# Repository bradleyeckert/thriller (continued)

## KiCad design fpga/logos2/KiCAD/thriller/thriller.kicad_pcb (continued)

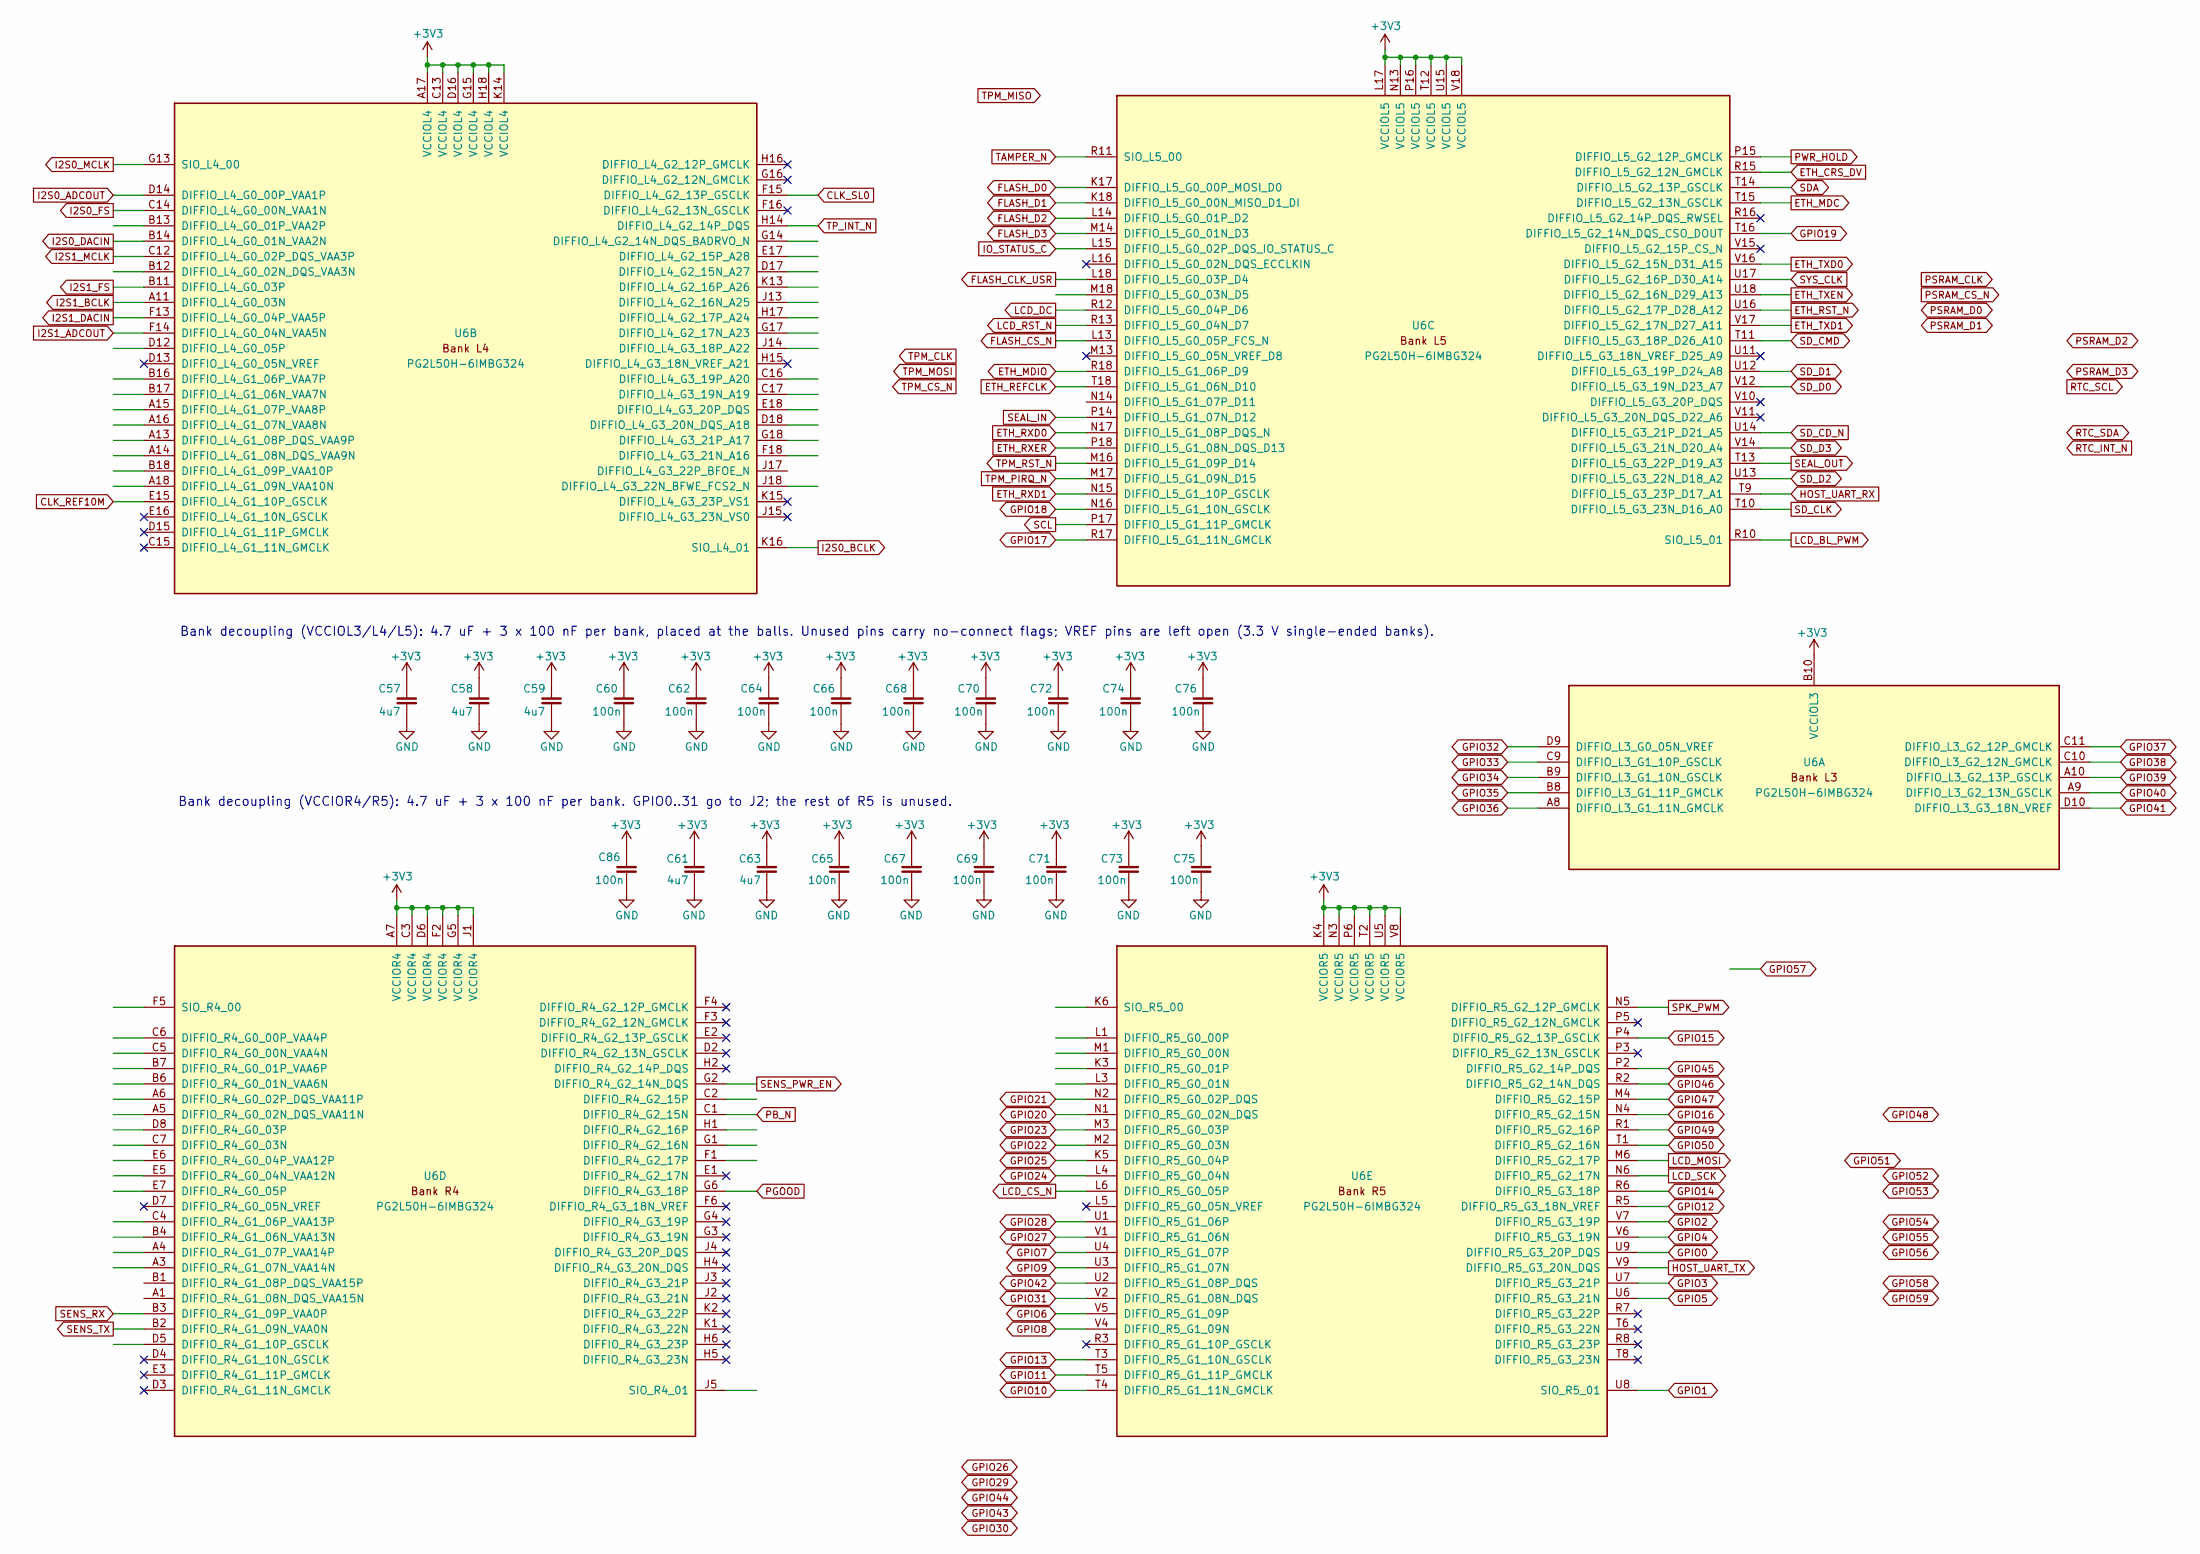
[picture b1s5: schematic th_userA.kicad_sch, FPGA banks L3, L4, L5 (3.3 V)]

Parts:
C57, C58, C59, C61, C63: 4u7; C_0603_1608Metric; LCSC C19666
C60, C62, C64, C65, C66, C67, C68, C69, C70, C71, C72, C73, C74, C75, C76, C86: 100n; C_0402_1005Metric; LCSC C1525
U6: PG2L50H-6IMBG324; BGA-324_15x15mm_Layout18x18_P0.8mm; MPN PG2L50H-6IMBG324

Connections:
CLK_REF10M: U6.E15 (DIFFIO_L4_G1_10P_GSCLK); also elsewhere on the board
CLK_SL0: U6.F15 (DIFFIO_L4_G2_13P_GSCLK); also elsewhere on the board
ETH_CRS_DV: U6.R15 (DIFFIO_L5_G2_12N_GMCLK); also elsewhere on the board
ETH_MDC: U6.T15 (DIFFIO_L5_G2_13N_GSCLK); also elsewhere on the board
ETH_MDIO: U6.R18 (DIFFIO_L5_G1_06P_D9); also elsewhere on the board
ETH_REFCLK: U6.T18 (DIFFIO_L5_G1_06N_D10); also elsewhere on the board
ETH_RST_N: U6.U16 (DIFFIO_L5_G2_17P_D28_A12); also elsewhere on the board
ETH_RXD0: U6.N17 (DIFFIO_L5_G1_08P_DQS_N); also elsewhere on the board
ETH_RXD1: U6.N15 (DIFFIO_L5_G1_10P_GSCLK); also elsewhere on the board
ETH_RXER: U6.P18 (DIFFIO_L5_G1_08N_DQS_D13); also elsewhere on the board
ETH_TXD0: U6.V16 (DIFFIO_L5_G2_15N_D31_A15); also elsewhere on the board
ETH_TXD1: U6.V17 (DIFFIO_L5_G2_17N_D27_A11); also elsewhere on the board
ETH_TXEN: U6.U18 (DIFFIO_L5_G2_16N_D29_A13); also elsewhere on the board
FLASH_CLK_USR: U6.L18 (DIFFIO_L5_G0_03P_D4); also elsewhere on the board
FLASH_CS_N: U6.L13 (DIFFIO_L5_G0_05P_FCS_N); also elsewhere on the board
FLASH_D0: U6.K17 (DIFFIO_L5_G0_00P_MOSI_D0); also elsewhere on the board
FLASH_D1: U6.K18 (DIFFIO_L5_G0_00N_MISO_D1_DI); also elsewhere on the board
FLASH_D2: U6.L14 (DIFFIO_L5_G0_01P_D2); also elsewhere on the board
FLASH_D3: U6.M14 (DIFFIO_L5_G0_01N_D3); also elsewhere on the board
GND: C57.2, C58.2, C59.2, C60.2, C61.2, C62.2, C63.2, C64.2, C65.2, C66.2, C67.2, C68.2, C69.2, C70.2, C71.2, C72.2, C73.2, C74.2, C75.2, C76.2, C86.2; also elsewhere on the board
GPIO0: U6.U9 (DIFFIO_R5_G3_20P_DQS); also elsewhere on the board
GPIO1: U6.U8 (SIO_R5_01); also elsewhere on the board
GPIO2: U6.V7 (DIFFIO_R5_G3_19P); also elsewhere on the board
GPIO3: U6.U7 (DIFFIO_R5_G3_21P); also elsewhere on the board
GPIO4: U6.V6 (DIFFIO_R5_G3_19N); also elsewhere on the board
GPIO5: U6.U6 (DIFFIO_R5_G3_21N); also elsewhere on the board
GPIO6: U6.V5 (DIFFIO_R5_G1_09P); also elsewhere on the board
GPIO7: U6.U4 (DIFFIO_R5_G1_07P); also elsewhere on the board
GPIO8: U6.V4 (DIFFIO_R5_G1_09N); also elsewhere on the board
GPIO9: U6.U3 (DIFFIO_R5_G1_07N); also elsewhere on the board
GPIO10: U6.T4 (DIFFIO_R5_G1_11N_GMCLK); also elsewhere on the board
GPIO11: U6.T5 (DIFFIO_R5_G1_11P_GMCLK); also elsewhere on the board
GPIO12: U6.R5 (DIFFIO_R5_G3_18N_VREF); also elsewhere on the board
GPIO13: U6.T3 (DIFFIO_R5_G1_10N_GSCLK); also elsewhere on the board
GPIO14: U6.R6 (DIFFIO_R5_G3_18P); also elsewhere on the board
GPIO15: U6.P4 (DIFFIO_R5_G2_13P_GSCLK); also elsewhere on the board
GPIO16: U6.N4 (DIFFIO_R5_G2_15N); also elsewhere on the board
GPIO17: U6.R17 (DIFFIO_L5_G1_11N_GMCLK); also elsewhere on the board
GPIO18: U6.N16 (DIFFIO_L5_G1_10N_GSCLK); also elsewhere on the board
GPIO19: U6.T16 (DIFFIO_L5_G2_14N_DQS_CSO_DOUT); also elsewhere on the board
GPIO20: U6.N1 (DIFFIO_R5_G0_02N_DQS); also elsewhere on the board
GPIO21: U6.N2 (DIFFIO_R5_G0_02P_DQS); also elsewhere on the board
GPIO22: U6.M2 (DIFFIO_R5_G0_03N); also elsewhere on the board
GPIO23: U6.M3 (DIFFIO_R5_G0_03P); also elsewhere on the board
GPIO24: U6.L4 (DIFFIO_R5_G0_04N); also elsewhere on the board
GPIO25: U6.K5 (DIFFIO_R5_G0_04P); also elsewhere on the board
GPIO27: U6.V1 (DIFFIO_R5_G1_06N); also elsewhere on the board
GPIO28: U6.U1 (DIFFIO_R5_G1_06P); also elsewhere on the board
GPIO31: U6.V2 (DIFFIO_R5_G1_08N_DQS); also elsewhere on the board
GPIO32: U6.D9 (DIFFIO_L3_G0_05N_VREF); also elsewhere on the board
GPIO33: U6.C9 (DIFFIO_L3_G1_10P_GSCLK); also elsewhere on the board
GPIO34: U6.B9 (DIFFIO_L3_G1_10N_GSCLK); also elsewhere on the board
GPIO35: U6.B8 (DIFFIO_L3_G1_11P_GMCLK); also elsewhere on the board
GPIO36: U6.A8 (DIFFIO_L3_G1_11N_GMCLK); also elsewhere on the board
GPIO37: U6.C11 (DIFFIO_L3_G2_12P_GMCLK); also elsewhere on the board
GPIO38: U6.C10 (DIFFIO_L3_G2_12N_GMCLK); also elsewhere on the board
GPIO39: U6.A10 (DIFFIO_L3_G2_13P_GSCLK); also elsewhere on the board
GPIO40: U6.A9 (DIFFIO_L3_G2_13N_GSCLK); also elsewhere on the board
GPIO41: U6.D10 (DIFFIO_L3_G3_18N_VREF); also elsewhere on the board
GPIO42: U6.U2 (DIFFIO_R5_G1_08P_DQS); also elsewhere on the board
GPIO45: U6.P2 (DIFFIO_R5_G2_14P_DQS); also elsewhere on the board
GPIO46: U6.R2 (DIFFIO_R5_G2_14N_DQS); also elsewhere on the board
GPIO47: U6.M4 (DIFFIO_R5_G2_15P); also elsewhere on the board
GPIO49: U6.R1 (DIFFIO_R5_G2_16P); also elsewhere on the board
GPIO50: U6.T1 (DIFFIO_R5_G2_16N); also elsewhere on the board
HOST_UART_RX: U6.T9 (DIFFIO_L5_G3_23P_D17_A1); also elsewhere on the board
HOST_UART_TX: U6.V9 (DIFFIO_R5_G3_20N_DQS); also elsewhere on the board
I2S0_ADCOUT: U6.D14 (DIFFIO_L4_G0_00P_VAA1P); also elsewhere on the board
I2S0_BCLK: U6.K16 (SIO_L4_01); also elsewhere on the board
I2S0_DACIN: U6.B14 (DIFFIO_L4_G0_01N_VAA2N); also elsewhere on the board
I2S0_FS: U6.C14 (DIFFIO_L4_G0_00N_VAA1N); also elsewhere on the board
I2S0_MCLK: U6.G13 (SIO_L4_00); also elsewhere on the board
I2S1_ADCOUT: U6.F14 (DIFFIO_L4_G0_04N_VAA5N); also elsewhere on the board
I2S1_BCLK: U6.A11 (DIFFIO_L4_G0_03N); also elsewhere on the board
I2S1_DACIN: U6.F13 (DIFFIO_L4_G0_04P_VAA5P); also elsewhere on the board
I2S1_FS: U6.B11 (DIFFIO_L4_G0_03P); also elsewhere on the board
I2S1_MCLK: U6.C12 (DIFFIO_L4_G0_02P_DQS_VAA3P); also elsewhere on the board
IO_STATUS_C: U6.L15 (DIFFIO_L5_G0_02P_DQS_IO_STATUS_C); also elsewhere on the board
LCD_BL_PWM: U6.R10 (SIO_L5_01); also elsewhere on the board
LCD_CS_N: U6.L6 (DIFFIO_R5_G0_05P); also elsewhere on the board
LCD_DC: U6.R12 (DIFFIO_L5_G0_04P_D6); also elsewhere on the board
LCD_MOSI: U6.M6 (DIFFIO_R5_G2_17P); also elsewhere on the board
LCD_RST_N: U6.R13 (DIFFIO_L5_G0_04N_D7); also elsewhere on the board
LCD_SCK: U6.N6 (DIFFIO_R5_G2_17N); also elsewhere on the board
PB_N: U6.C1 (DIFFIO_R4_G2_15N); also elsewhere on the board
PGOOD: U6.G6 (DIFFIO_R4_G3_18P); also elsewhere on the board
PWR_HOLD: U6.P15 (DIFFIO_L5_G2_12P_GMCLK); also elsewhere on the board
SCL: U6.P17 (DIFFIO_L5_G1_11P_GMCLK); also elsewhere on the board
SDA: U6.T14 (DIFFIO_L5_G2_13P_GSCLK); also elsewhere on the board
SD_CD_N: U6.U14 (DIFFIO_L5_G3_21P_D21_A5); also elsewhere on the board
SD_CLK: U6.T10 (DIFFIO_L5_G3_23N_D16_A0); also elsewhere on the board
SD_CMD: U6.T11 (DIFFIO_L5_G3_18P_D26_A10); also elsewhere on the board
SD_D0: U6.V12 (DIFFIO_L5_G3_19N_D23_A7); also elsewhere on the board
SD_D1: U6.U12 (DIFFIO_L5_G3_19P_D24_A8); also elsewhere on the board
SD_D2: U6.U13 (DIFFIO_L5_G3_22N_D18_A2); also elsewhere on the board
SD_D3: U6.V14 (DIFFIO_L5_G3_21N_D20_A4); also elsewhere on the board
SEAL_IN: U6.P14 (DIFFIO_L5_G1_07N_D12); also elsewhere on the board
SEAL_OUT: U6.T13 (DIFFIO_L5_G3_22P_D19_A3); also elsewhere on the board
SENS_PWR_EN: U6.G2 (DIFFIO_R4_G2_14N_DQS); also elsewhere on the board
SENS_RX: U6.B3 (DIFFIO_R4_G1_09P_VAA0P); also elsewhere on the board
SENS_TX: U6.B2 (DIFFIO_R4_G1_09N_VAA0N); also elsewhere on the board
SPK_PWM: U6.N5 (DIFFIO_R5_G2_12P_GMCLK); also elsewhere on the board
SYS_CLK: U6.U17 (DIFFIO_L5_G2_16P_D30_A14); also elsewhere on the board
TAMPER_N: U6.R11 (SIO_L5_00); also elsewhere on the board
TPM_PIRQ_N: U6.M17 (DIFFIO_L5_G1_09N_D15); also elsewhere on the board
TPM_RST_N: U6.M16 (DIFFIO_L5_G1_09P_D14); also elsewhere on the board
TP_INT_N: U6.H14 (DIFFIO_L4_G2_14P_DQS); also elsewhere on the board

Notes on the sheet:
Bank decoupling (VCCIOR4/R5): 4.7 uF + 3 x 100 nF per bank. GPIO0..31 go to J2; the rest of R5 is unused.
Bank decoupling (VCCIOL3/L4/L5): 4.7 uF + 3 x 100 nF per bank, placed at the balls. Unused pins carry no-connect flags; VREF pins are left open (3.3 V single-ended banks).

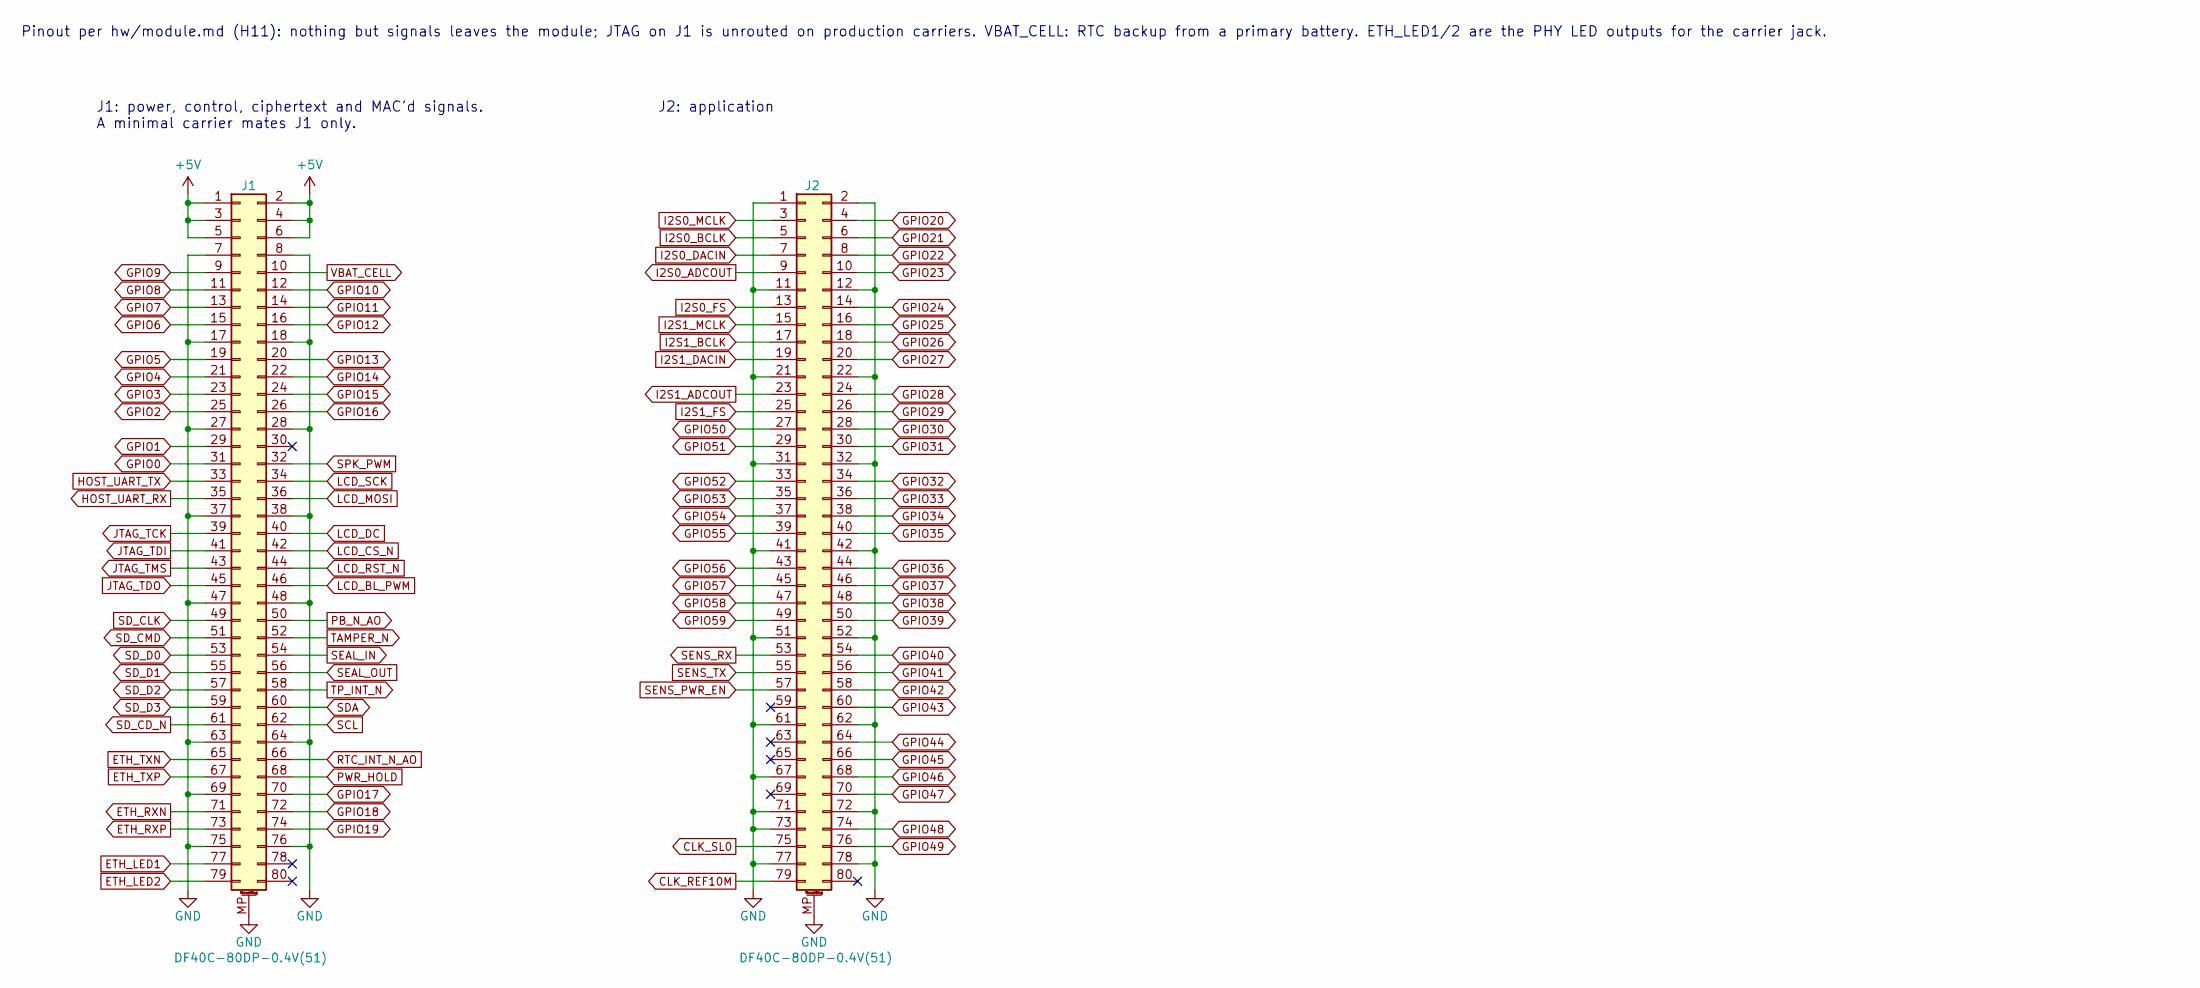
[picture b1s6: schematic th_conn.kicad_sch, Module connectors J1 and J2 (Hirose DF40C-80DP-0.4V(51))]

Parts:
J1, J2: DF40C-80DP-0.4V(51); Hirose_DF40C-80DP-0.4V_2x40-1MP_P0.4mm; MPN DF40C-80DP-0.4V(51)

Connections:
+5V: J1.1, J1.2, J1.3, J1.4, J1.5, J1.6; also elsewhere on the board
CLK_REF10M: J2.79; also elsewhere on the board
CLK_SL0: J2.75; also elsewhere on the board
ETH_LED1: J1.77; also elsewhere on the board
ETH_LED2: J1.79; also elsewhere on the board
ETH_RXN: J1.71; also elsewhere on the board
ETH_RXP: J1.73; also elsewhere on the board
ETH_TXN: J1.65; also elsewhere on the board
ETH_TXP: J1.67; also elsewhere on the board
GND: J1.7, J1.8, J1.17, J1.18, J1.27, J1.28, J1.37, J1.38, J1.47, J1.48, J1.63, J1.64, J1.69, J1.75, J1.76, J1.MP (MountPin), J2.1, J2.2, J2.11, J2.12, J2.21, J2.22, J2.31, J2.32, J2.41, J2.42, J2.51, J2.52, J2.61, J2.62, J2.67, J2.71, J2.72, J2.73, J2.77, J2.78, J2.MP (MountPin); also elsewhere on the board
GPIO0: J1.31; also elsewhere on the board
GPIO1: J1.29; also elsewhere on the board
GPIO2: J1.25; also elsewhere on the board
GPIO3: J1.23; also elsewhere on the board
GPIO4: J1.21; also elsewhere on the board
GPIO5: J1.19; also elsewhere on the board
GPIO6: J1.15; also elsewhere on the board
GPIO7: J1.13; also elsewhere on the board
GPIO8: J1.11; also elsewhere on the board
GPIO9: J1.9; also elsewhere on the board
GPIO10: J1.12; also elsewhere on the board
GPIO11: J1.14; also elsewhere on the board
GPIO12: J1.16; also elsewhere on the board
GPIO13: J1.20; also elsewhere on the board
GPIO14: J1.22; also elsewhere on the board
GPIO15: J1.24; also elsewhere on the board
GPIO16: J1.26; also elsewhere on the board
GPIO17: J1.70; also elsewhere on the board
GPIO18: J1.72; also elsewhere on the board
GPIO19: J1.74; also elsewhere on the board
GPIO20: J2.4; also elsewhere on the board
GPIO21: J2.6; also elsewhere on the board
GPIO22: J2.8; also elsewhere on the board
GPIO23: J2.10; also elsewhere on the board
GPIO24: J2.14; also elsewhere on the board
GPIO25: J2.16; also elsewhere on the board
GPIO26: J2.18
GPIO27: J2.20; also elsewhere on the board
GPIO28: J2.24; also elsewhere on the board
GPIO29: J2.26
GPIO30: J2.28
GPIO31: J2.30; also elsewhere on the board
GPIO32: J2.34; also elsewhere on the board
GPIO33: J2.36; also elsewhere on the board
GPIO34: J2.38; also elsewhere on the board
GPIO35: J2.40; also elsewhere on the board
GPIO36: J2.44; also elsewhere on the board
GPIO37: J2.46; also elsewhere on the board
GPIO38: J2.48; also elsewhere on the board
GPIO39: J2.50; also elsewhere on the board
GPIO40: J2.54; also elsewhere on the board
GPIO41: J2.56; also elsewhere on the board
GPIO42: J2.58; also elsewhere on the board
GPIO43: J2.60
GPIO44: J2.64
GPIO45: J2.66; also elsewhere on the board
GPIO46: J2.68; also elsewhere on the board
GPIO47: J2.70; also elsewhere on the board
GPIO48: J2.74
GPIO49: J2.76; also elsewhere on the board
GPIO50: J2.27; also elsewhere on the board
GPIO51: J2.29
GPIO52: J2.33
GPIO53: J2.35
GPIO54: J2.37
GPIO55: J2.39
GPIO56: J2.43
GPIO57: J2.45
GPIO58: J2.47
GPIO59: J2.49
HOST_UART_RX: J1.35; also elsewhere on the board
HOST_UART_TX: J1.33; also elsewhere on the board
I2S0_ADCOUT: J2.9; also elsewhere on the board
I2S0_BCLK: J2.5; also elsewhere on the board
I2S0_DACIN: J2.7; also elsewhere on the board
I2S0_FS: J2.13; also elsewhere on the board
I2S0_MCLK: J2.3; also elsewhere on the board
I2S1_ADCOUT: J2.23; also elsewhere on the board
I2S1_BCLK: J2.17; also elsewhere on the board
I2S1_DACIN: J2.19; also elsewhere on the board
I2S1_FS: J2.25; also elsewhere on the board
I2S1_MCLK: J2.15; also elsewhere on the board
JTAG_TCK: J1.39; also elsewhere on the board
JTAG_TDI: J1.41; also elsewhere on the board
JTAG_TDO: J1.45; also elsewhere on the board
JTAG_TMS: J1.43; also elsewhere on the board
LCD_BL_PWM: J1.46; also elsewhere on the board
LCD_CS_N: J1.42; also elsewhere on the board
LCD_DC: J1.40; also elsewhere on the board
LCD_MOSI: J1.36; also elsewhere on the board
LCD_RST_N: J1.44; also elsewhere on the board
LCD_SCK: J1.34; also elsewhere on the board
PB_N_AO: J1.50
PWR_HOLD: J1.68; also elsewhere on the board
RTC_INT_N_AO: J1.66
SCL: J1.62; also elsewhere on the board
SDA: J1.60; also elsewhere on the board
SD_CD_N: J1.61; also elsewhere on the board
SD_CLK: J1.49; also elsewhere on the board
SD_CMD: J1.51; also elsewhere on the board
SD_D0: J1.53; also elsewhere on the board
SD_D1: J1.55; also elsewhere on the board
SD_D2: J1.57; also elsewhere on the board
SD_D3: J1.59; also elsewhere on the board
SEAL_IN: J1.54; also elsewhere on the board
SEAL_OUT: J1.56; also elsewhere on the board
SENS_PWR_EN: J2.57; also elsewhere on the board
SENS_RX: J2.53; also elsewhere on the board
SENS_TX: J2.55; also elsewhere on the board
SPK_PWM: J1.32; also elsewhere on the board
TAMPER_N: J1.52; also elsewhere on the board
TP_INT_N: J1.58; also elsewhere on the board
VBAT_CELL: J1.10; also elsewhere on the board

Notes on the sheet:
Pinout per hw/module.md (H11): nothing but signals leaves the module; JTAG on J1 is unrouted on production carriers. VBAT_CELL: RTC backup from a primary battery. ETH_LED1/2 are the PHY LED outputs for the carrier jack.
J1: power, control, ciphertext and MAC'd signals. A minimal carrier mates J1 only.
J2: application

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
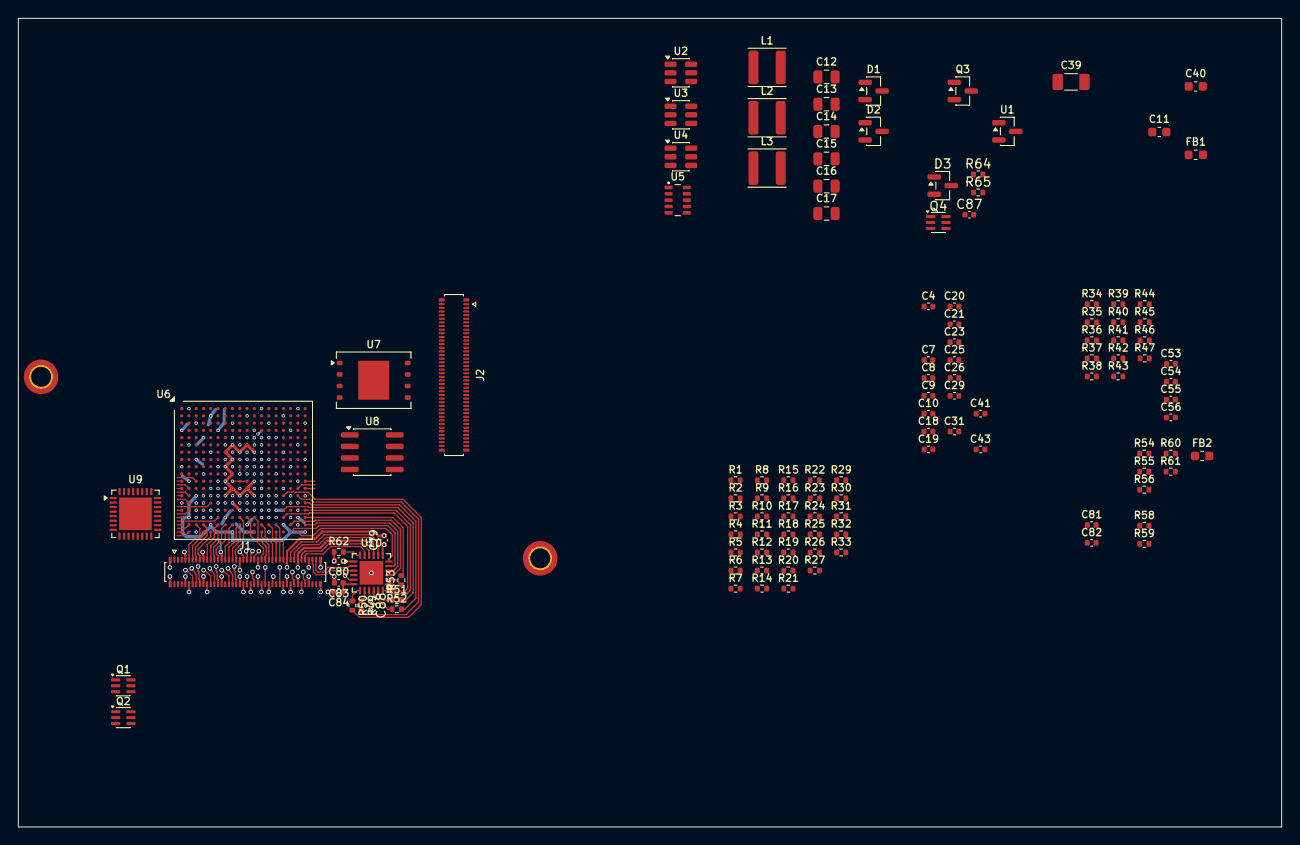
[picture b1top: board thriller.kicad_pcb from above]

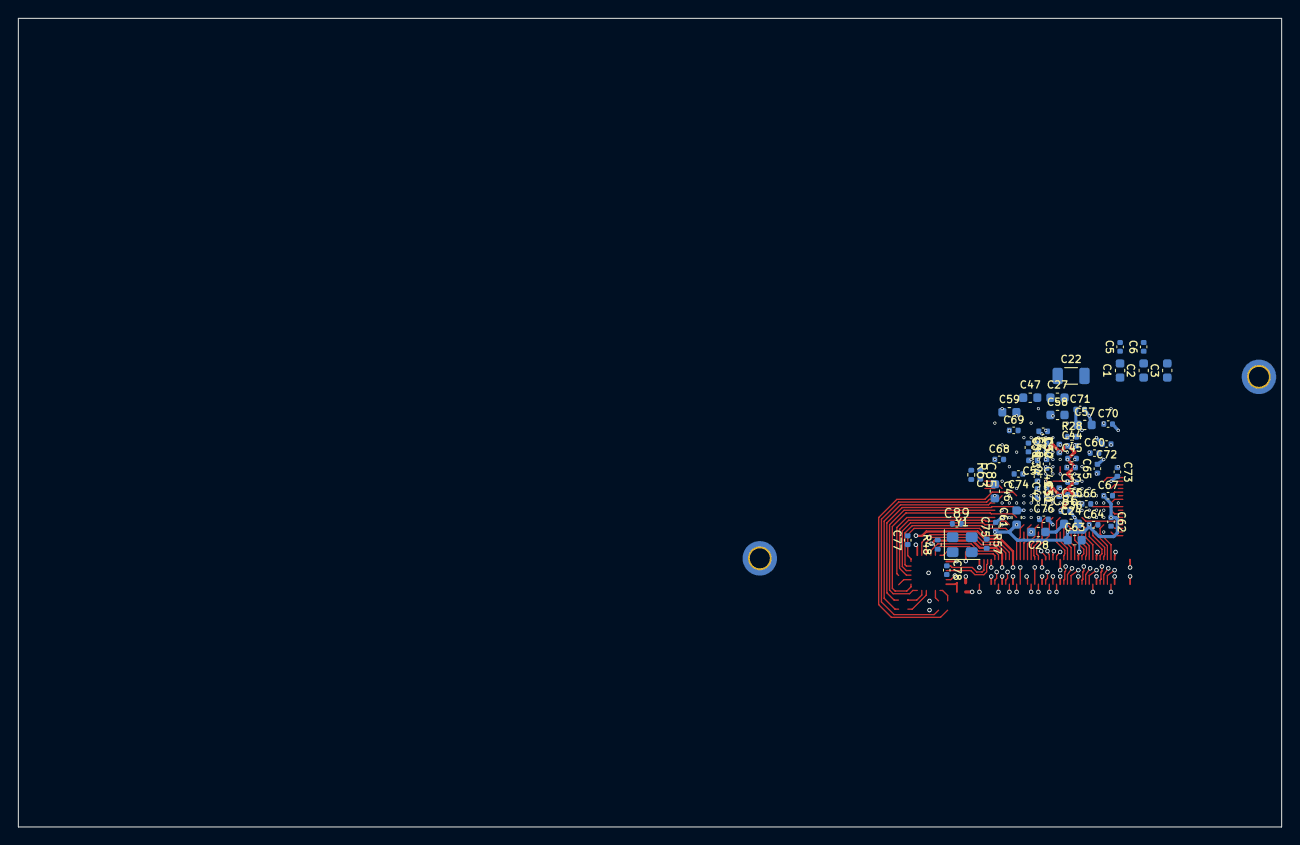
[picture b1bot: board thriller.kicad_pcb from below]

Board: 6 copper layers, 139.2 x 89.1 mm, 181 parts (57 on the bottom side), 171 nets.

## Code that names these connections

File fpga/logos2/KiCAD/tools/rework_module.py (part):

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    # bank L4: J2's audio, display, speaker, carrier clocks, first GPIO
    g('DIFFIO_L4_G1_10P_GSCLK', 'CLK_REF10M'); g('DIFFIO_L4_G2_13P_GSCLK', 'CLK_SI0'); g('DIFFIO_L4_G1_11P_GMCLK', 'CLK_SI1')
    l4 = [f'AUD{i}_{s}' for i in (1, 2) for s in ('MCLK', 'BCLK', 'FS', 'ADCOUT', 'DACIN', 'SCL', 'SDA')] + \
         ['LCD_SCK', 'LCD_MOSI', 'LCD_DC', 'LCD_CS_N', 'LCD_RST_N', 'LCD_BL_PWM', 'TP_SCL', 'TP_SDA', 'TP_INT_N', 'SPK_PWM'] + [f'GPIO{i}' for i in range(0, 14)]
    r5 = [f'GPIO{i}' for i in range(14, 32)]
    def pool(bank):
        names = sorted((v[1] for b, v in pins.items() if v[0] == bank and byname[v[1]] not in A),
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        if sh.prop(s, 'Reference') == 'Y1':
            set_prop(s, 'Value', '25MHz'); set_prop(s, 'LCSC', ''); set_prop(s, 'MPN', '25 MHz 3225 CMOS XO, 3.3 V (choose LCSC part)')
            set_prop(s, 'Description', 'Crystal oscillator 25 MHz 3225, the module clock: FPGA PLL and the PHY (CLKIN)')
    # VBAT from J1: a global label on the VBAT_CELL net; JTAG as global nets
    for l in list(sh.items('label')):
        nm = unq(l[1]); x, y = label_pos(l); at = find1(l, 'at'); rot = int(float(at[3]))
        if nm in ('VBAT_CELL', 'JTAG_TCK', 'JTAG_TMS', 'JTAG_TDI', 'JTAG_TDO', 'OSC_OUT'):
            sh.remove(l); sh.tree.append(glabel(nm if nm != 'OSC_OUT' else 'SYS_CLK', x, y, rot))
    ensure_lib(sh, 'thriller:ST33KTPM2X', tpm)
    embed_common(sh)
    su = suuid['th_base.kicad_sch']
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        sh.tree.append(glabel(net, p2[0], p2[1], 0))
    # RST pull-down so the TPM stays in reset until the boot ROM drives the line (DB5174: RST must not float; the FPGA drives it)
    p1, p2 = res('10k', tx + 38, ty + 12.7, 0, 'Resistor 10 kOhm 0402, TPM RST pull-down')
    sh.tree.append(glabel('TPM_RST_N', p1[0], p1[1], 90)); sh.tree.append(power_sym('GND', p2[0], p2[1], su))
    # PIRQ pull-up, mandatory for standby current (DB5174 figure 3)
    p1, p2 = res('10k', tx + 48, ty + 12.7, 0, 'Resistor 10 kOhm 0402, TPM PIRQ pull-up (mandatory, DB5174 4.3)')
    sh.tree.append(power_sym('+3V3', p1[0], p1[1], su)); sh.tree.append(glabel('TPM_PIRQ_N', p2[0], p2[1], 270))
    # 56 pF on CS so CLK is low when CS falls (DB5174 4.2); optional
    c = sym_instance('thriller:C', refs.next('C'), '56p', tx + 58, ty + 12.7, 0, 1, su, ['1', '2'], CAP_PROPS['56p']); sh.tree.append(c)
    sh.tree.append(glabel('TPM_CS_N', tx + 58, ty + 12.7 - 3.81, 90)); sh.tree.append(power_sym('GND', tx + 58, ty + 12.7 + 3.81, su))
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        if nm in ('PHY_LED1', 'PHY_LED2'):
            sh.remove(l); sh.tree.append(glabel('ETH_LED' + nm[-1], x, y, rot))
        if nm == 'PHY_XI':   # crystal input becomes the module clock input; the crystal load cap goes with the crystal
            sh.remove(l); sh.tree.append(glabel('SYS_CLK', x, y, rot))
        if nm == 'PHY_XO':
            sh.remove(l)
    prune(sh)
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    refs = RefCounter({'C': 220})
    for i, (val, rail) in enumerate([('4u7', '+3V3')] * 2 + [('100n', '+3V3')] * 6):
        add_cap(sh, refs, val, rail, 40 + i * 12, 360, su)
    sh.tree.append(text_item('Bank decoupling (VCCIOR4/R5): 4.7 uF + 3 x 100 nF per bank. GPIO0..31 go to J2; the rest of R5 is unused.', 20, 20, 1.5))
    save(sh, 'th_userB.kicad_sch')
    # th_fpga (new): config/JTAG/ADC, core power, ground
    sh = fpga_sheet('FPGA configuration, JTAG, core power and ground', [6, 7, 8], 'th_fpga.kicad_sch')
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    conn_uuid = str(_uuid.uuid5(_uuid.NAMESPACE_URL, 'thriller/th_conn')); su = conn_uuid
    lp = sh.libs['thriller:DF40C-80DP']
    for ref, X, assign, note in (('J1', 90, j1_assignment(), 'J1: power, control, ciphertext and MAC\'d signals. A minimal carrier mates J1 only.'),
                                 ('J2', 260, j2_assignment(), 'J2: audio (plaintext I2S), display, speaker, carrier clocks, GPIO0..31.')):
        inst = sym_instance('thriller:DF40C-80DP', ref, 'DF40C-80DP-0.4V(51)', X, 150, 0, 1, su, [str(n) for n in range(1, 81)],
                            {'Footprint': 'Connector_Hirose:Hirose_DF40C-80DP-0.4V_2x40_P0.40mm', 'MPN': 'DF40C-80DP-0.4V(51)', 'LCSC': ''})
        sh.tree.append(inst)
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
